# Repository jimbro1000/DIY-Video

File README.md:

# DIY Video #

The DIY Video project is an attempt to define a reusable video "chip" with
modular components. The concept is to limit the design to regular 74LS
ICs.

The goal is a design that can be plugged into most (if not all) 8-bit
computers.

The minimal design permits a system that can switch between a simple
text mode and bitmap mode with a usable screen resolution of 320x200 pixels.
Output is unterminated RGB that can be transformed into an appropriate
format as required

## Design Concepts ##

Each major component of the video system is deliberately isolated so
that a change in one area should not require rework elsewhere. This rule
is broken in some places but is respected as much as possible

The core of the system is a pair of counters that track the X and Y 
position of the "beam". These counters are then used to define the
frame timing (sync and blank) and the viewport position on the screen.

The frame timing also controls what video source makes it to the output
as the sync and blank phases of the signal fall under timing control.

The bitmap renderer uses the pixel counters to generate a palette index
based on either a 1, 2 or 4 bit length value. The index is turned into
RGB using a separate pair of modules that generate 16 distinct RGB values
and a decoder that switches the RGB output between the 16 different
palette options

Independently to all this is the memory controller, actually a repeated
module that provisions different, parallel rendering mechanisms. From
the perspective of the video system each has its own address register
and can be accessed independently of the others - so the bitmap, tile
and sprite data can be operated separately without impacting the timing
of the other.

Externally the different blocks of memory needed to be mapped into the
hosts address space. To facilitate this the different memory blocks
are first selected by a device select signal and are then (optionally)
paged to ease the host burden. 

This approach makes the internal address very wide - each memory block is
a maximum of 32K and with distinct address buses and data buses the burden
for the video system is high but the length and distribution of those
buses can be minimised leaving just the palette values as the the 
interconnect rather than wide data and address buses

The current design respects five different addressable sub-devices
Bitmap memory  
Tile memory  
Sprite memory  
Font generator  
Control registers  

Only the bitmap and control registers are currently implemented.

The font generator in initial design iterations will be a simple eprom that
does not require external addressing

## Roadmap ##

### Stage 1 ###

The initial design stage is to define the hardware and interfaces, the broad
timing requirements and what modules are dependent. The goal is to achieve
a design that can be tested in self-contained modules, that together can
implement a basic bitmap based video generator.

### Stage 2 ###

The initial design will be verified and refined to prove that the modules work.
No attempt to integrate the modules will be attempted at this stage. Signal
and power requirements will be added to the design

### Stage 3 ###

Modules will be implemented as independent PCBs to be re-verified. A backplane
to integrate the modules will be needed with scope to extend the design to 
include other sub-systems

### Stage 4 ###

This is the first opportunity to integrate the entire set of modules defined.
To provide a usable display that can be verified the system will also need
to be integrated with a host computer to drive the video memory content

## Test Progress ##

### Simulation ###

* Position Counters (verilog, CRUMB)
* ViewPort (Verilog)
* Bitmap Data Counters (Verilog)

## License ##

This project is licensed under CC BY-SA 4.0
<https://creativecommons.org/licenses/by-sa/4.0/>

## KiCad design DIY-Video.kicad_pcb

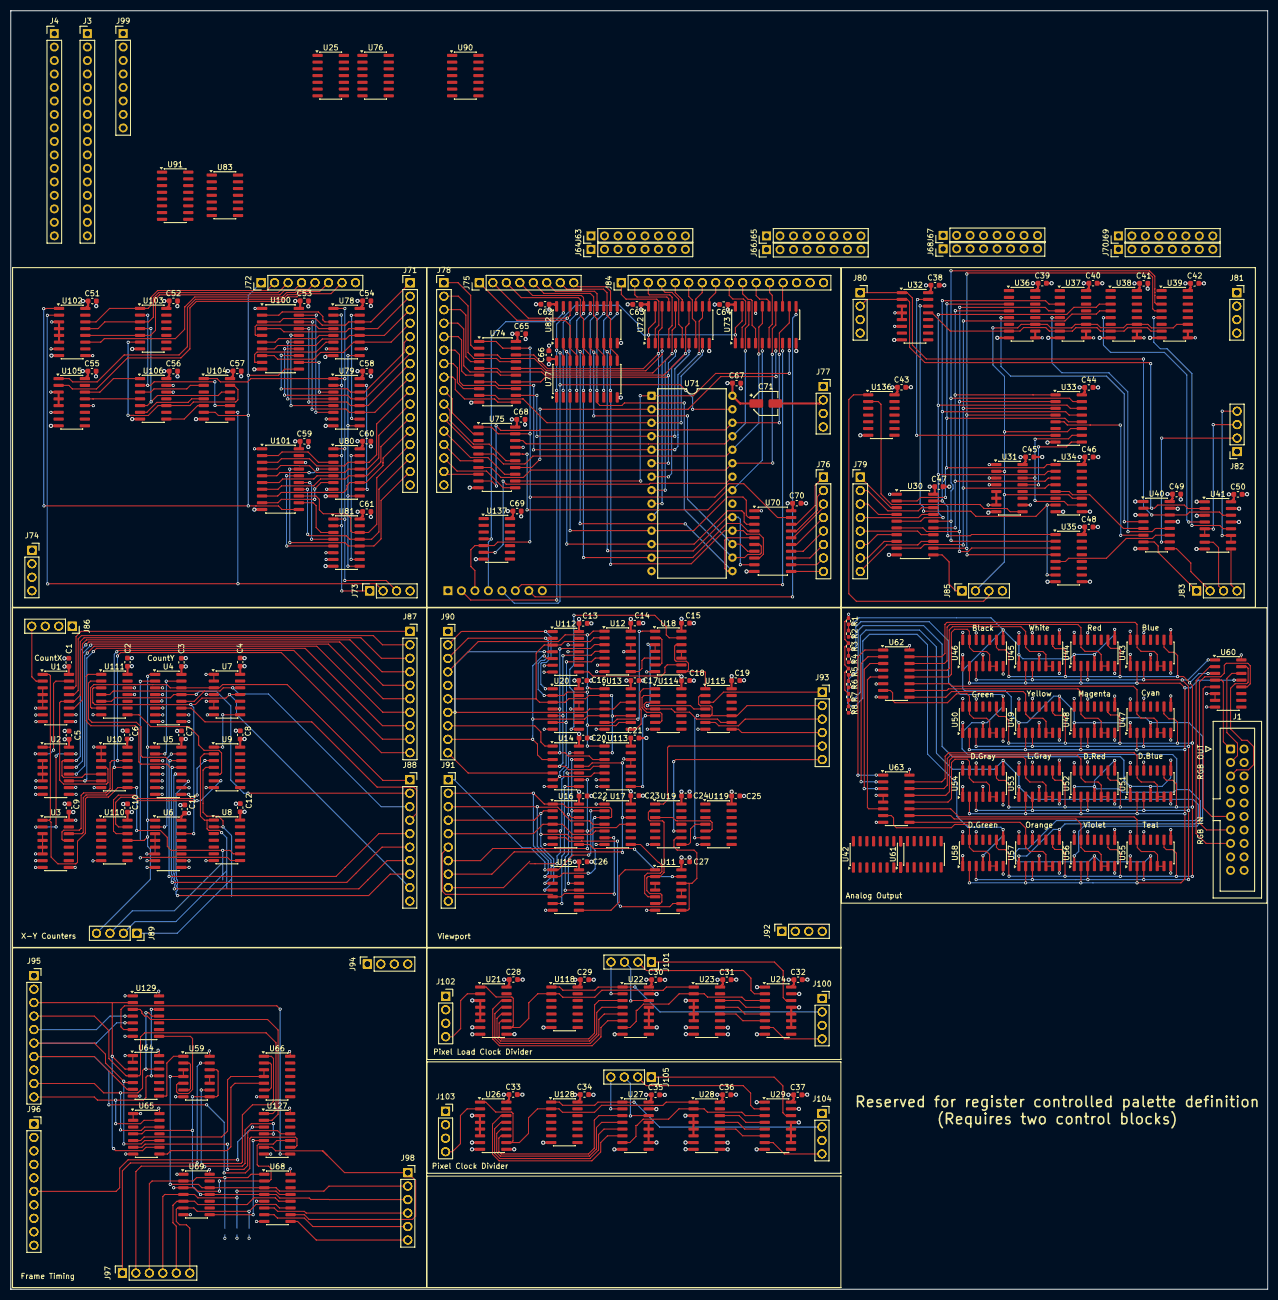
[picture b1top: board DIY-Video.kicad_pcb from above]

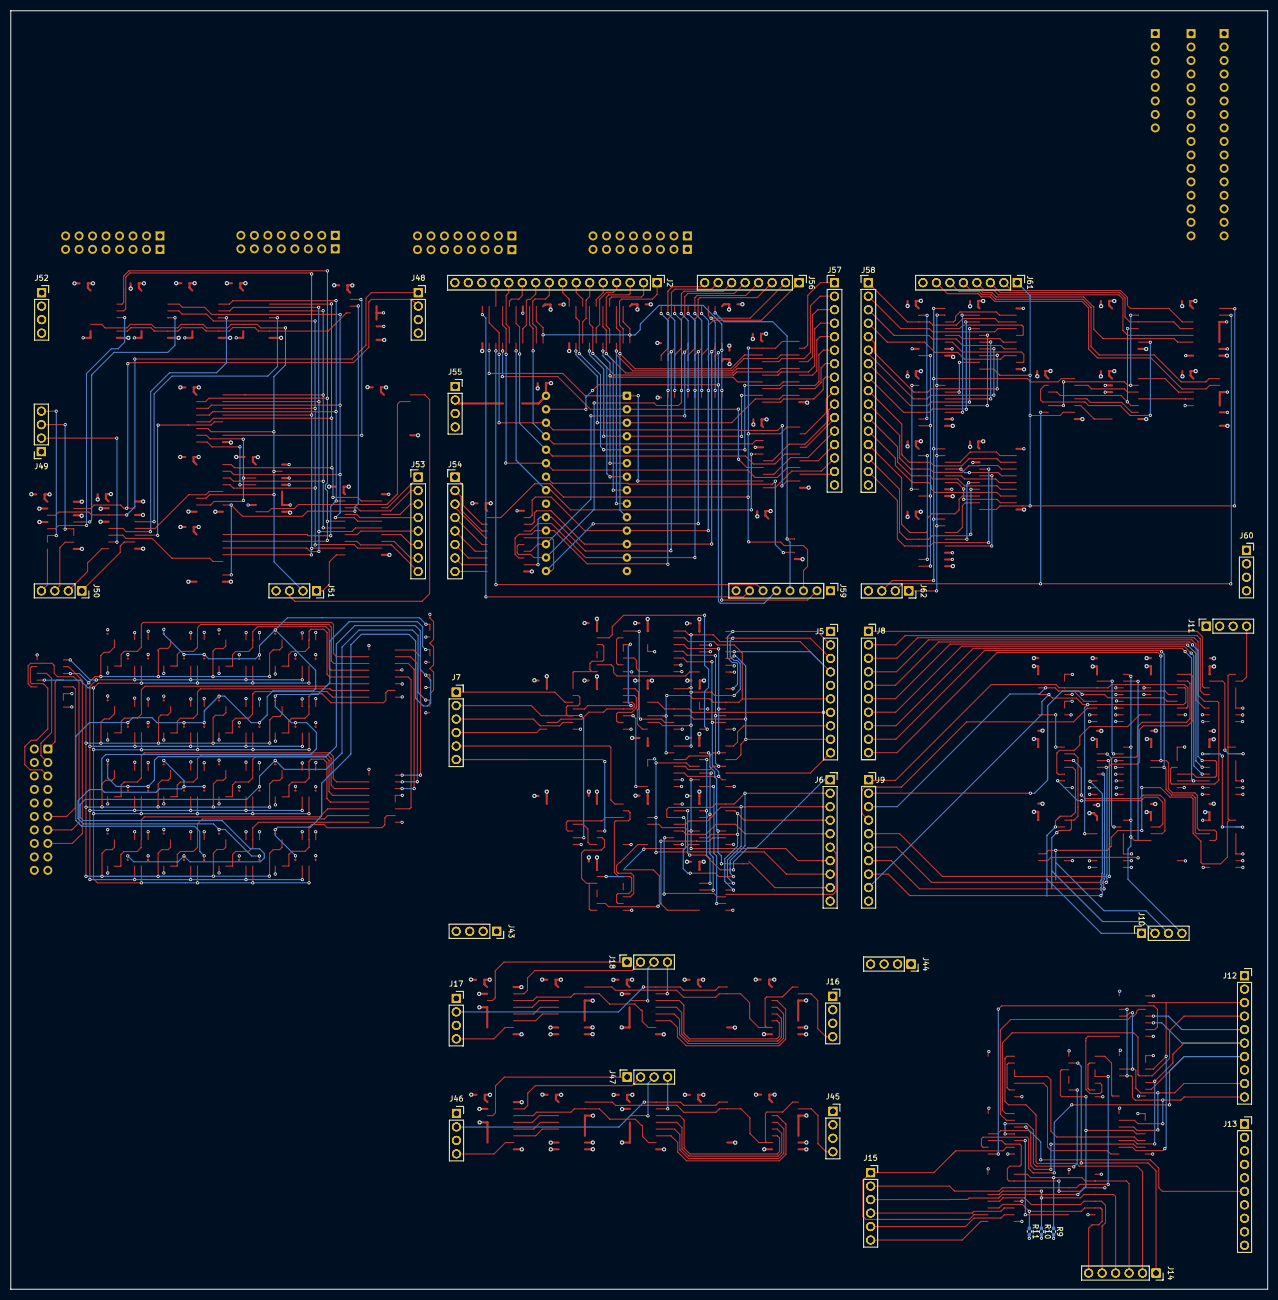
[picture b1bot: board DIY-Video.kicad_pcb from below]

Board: 4 copper layers, 236.8 x 240.9 mm, 315 parts (38 on the bottom side), 422 nets.

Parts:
C1, C2, C3, C4, C5, C6, C7, C8, C9, C10, C11, C12, C13, C14, C15, C16, C17, C18, C19, C20, C21, C22, C23, C24, C25, C26, C27, C28, C29, C30, C31, C32, C33, C34, C35, C36, C37, C38, C39, C40, C41, C42, C43, C44, C45, C46, C47, C48, C49, C50, C51, C52, C53, C54, C55, C56, C57, C58, C59, C60, C61, C62, C63, C64, C65, C66, C67, C68, C69, C70: 10nF; C_0603_1608Metric
C71: 4.7uF; CP_Elec_4x3
J1: VIDEO IO; IDC-Header_2x10_P2.54mm_Vertical
J2, J3, J84: Host Address Bus; PinHeader_1x16_P2.54mm_Vertical
J4: Host Control Bus; PinHeader_1x16_P2.54mm_Vertical
J5, J8, J12, J87, J90, J95: posX; PinSocket_1x10_P2.54mm_Vertical
J6, J9, J13, J88, J91, J96: posY; PinSocket_1x10_P2.54mm_Vertical
J7, J93: ViewportTriggers; PinSocket_1x06_P2.54mm_Vertical
J10, J89: PosResets; PinSocket_1x04_P2.54mm_Vertical
J11, J16, J45, J52, J81, J86, J102, J103: Power and Clock; PinSocket_1x04_P2.54mm_Vertical
J14, J97: TimingTriggers; PinSocket_1x06_P2.54mm_Vertical
J15, J98: ViewportOutput; PinSocket_1x06_P2.54mm_Vertical
J17, J46, J51, J62, J73, J85, J100, J104: Triggers; PinSocket_1x04_P2.54mm_Vertical
J18, J47, J48, J80, J101, J105: OpMode; PinSocket_1x04_P2.54mm_Vertical
J43, J44, J55, J60, J74, J77, J92, J94: Power; PinSocket_1x04_P2.54mm_Vertical
J49, J82: Default Palette; PinSocket_1x04_P2.54mm_Vertical
J50, J83: Output Palette; PinSocket_1x04_P2.54mm_Vertical
J53, J54, J76, J79: BDBus; PinHeader_1x08_P2.54mm_Vertical
J56, J75, J99: XDBus; PinHeader_1x08_P2.54mm_Vertical
J57, J58, J71, J78: BitmapAddress; PinHeader_1x16_P2.54mm_Vertical
J59: Control; PinHeader_1x08_P2.54mm_Vertical
J61, J72: RowCountControl; PinHeader_1x08_P2.54mm_Vertical
J63: Reg0; PinHeader_1x08_P2.54mm_Vertical
J64: Reg1; PinHeader_1x08_P2.54mm_Vertical
J65: Reg2; PinHeader_1x08_P2.54mm_Vertical
J66: Reg3; PinHeader_1x08_P2.54mm_Vertical
J67: Reg4; PinHeader_1x08_P2.54mm_Vertical
J68: Reg5; PinHeader_1x08_P2.54mm_Vertical
J69: Reg6; PinHeader_1x08_P2.54mm_Vertical
J70: Reg7; PinHeader_1x08_P2.54mm_Vertical
NT1, NT2, NT3, NT4, NT5, NT6, NT7, NT8, NT9, NT10, NT11, NT12, NT13, NT14, NT15, NT16, NT17, NT18, NT19, NT20, NT21, NT22, NT23, NT24, NT25, NT26, NT27, NT28, NT29, NT30, NT31, NT32, NT33, NT34, NT35, NT36, NT37, NT38, NT39, NT40, NT41, NT42, NT43, NT44, NT45, NT46, NT47, NT48: NetTie_2; NetTie-2_SMD_Pad0.4mm
R1, R3, R8: 100R; R_0402_1005Metric_Pad0.72x0.64mm_HandSolder
R2, R7: 200R; R_0402_1005Metric_Pad0.72x0.64mm_HandSolder
R4: 75R; R_0402_1005Metric_Pad0.72x0.64mm_HandSolder
R5: 180R; R_0402_1005Metric_Pad0.72x0.64mm_HandSolder
R6: 50R; R_0402_1005Metric_Pad0.72x0.64mm_HandSolder
R9, R10, R11: 4K7; R_0402_1005Metric_Pad0.72x0.64mm_HandSolder
U1, U2, U3, U4, U5, U6, U21, U23, U26, U28, U31, U78, U79, U80, U81, U102: 74LS163; SOIC-16_3.9x9.9mm_P1.27mm
U7, U10, U12, U15, U17, U20, U64, U69, U111, U112, U113, U129: 74LS30; SO-14_3.9x8.65mm_P1.27mm
U8, U14, U76: 74LS04; SO-14_3.9x8.65mm_P1.27mm
U9, U19, U115: 74LS32; SO-14_3.9x8.65mm_P1.27mm
U11, U18, U59, U66, U114: 74LS00; SO-14_3.9x8.65mm_P1.27mm
U13, U16, U65: 74LS20; SO-14_3.9x8.65mm_P1.27mm
U22, U24, U27, U29: 74LS253; SOIC-16_3.9x9.9mm_P1.27mm
U25, U106: 74LS32; SOIC-14_3.9x8.7mm_P1.27mm
U30: 74LS373; SO-20_5.3x12.6mm_P1.27mm
U32, U42, U62, U63, U105: 74LS138; SOIC-16_3.9x9.9mm_P1.27mm
U33, U34, U35, U36, U37, U38, U39: 74LS151; SOIC-16_3.9x9.9mm_P1.27mm
U40, U41: 74LS153; SOIC-16_3.9x9.9mm_P1.27mm
U43, U44, U45, U46, U47, U48, U49, U50, U51, U52, U53, U54, U55, U56, U57, U58: CD4066BM; SO-14_3.9x8.65mm_P1.27mm
U60: 4053; SOIC-16_3.9x9.9mm_P1.27mm
U61: 74LS21; SO-14_3.9x8.65mm_P1.27mm
U68: 74LS148; SOIC-16_3.9x9.9mm_P1.27mm
U70: 74LS245; SO-20_5.3x12.6mm_P1.27mm
U71: CY62256-70PC; DIP-28_W15.24mm
U72, U73, U74, U75, U77, U82: 74LS244; SO-20_5.3x12.6mm_P1.27mm
U83, U90, U110: 74LS08; SO-14_3.9x8.65mm_P1.27mm
U91: 74ALS138; SOIC-16_3.9x9.9mm_P1.27mm
U100, U101: 74LS374; SO-20_5.3x12.6mm_P1.27mm
U103, U118, U127, U128, U136: 74LS04; SOIC-14_3.9x8.7mm_P1.27mm
U104: 74LS21; SOIC-14_3.9x8.7mm_P1.27mm
U119, U137: 74LS08; SOIC-14_3.9x8.7mm_P1.27mm

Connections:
14M: J11.4, J16.4, J45.4, J86.4, J102.4, J103.4, U1.2 (CP), U21.2 (CP), U26.2 (CP)
+1V2: NT25.1, NT26.1, NT27.1, NT47.1, NT48.1, R5.2, R6.1
+1V5: NT31.1, NT36.1, NT38.1, NT41.1, R7.2, R8.1
+2V5: NT23.1, NT24.1, NT28.1, NT29.1, NT30.1, NT43.1, NT45.1, R3.2, R4.1
+3.3V: NT4.1, NT5.1, NT6.1, NT7.1, NT12.1, NT14.1, NT16.1, NT17.1, NT19.1, NT21.1, NT40.1, R1.2, R2.1
+5V: C1.1, C2.1, C3.1, C4.1, C5.1, C6.1, C7.1, C8.1, C9.1, C10.1, C11.1, C12.1, C13.1, C14.1, C15.1, C16.1, C17.1, C18.1, C19.1, C20.1, C21.1, C22.1, C23.1, C24.1, C25.1, C26.1, C27.1, C28.1, C29.1, C30.1, C31.1, C32.1, C33.1, C34.1, C35.1, C36.1, C37.1, C38.1, C39.1, C40.1, C41.1, C42.1, C43.1, C44.1, C45.1, C46.1, C47.1, C48.1, C49.1, C50.1, C51.1, C52.1, C53.1, C54.1, C55.1, C56.1, C57.1, C58.1, C59.1, C60.1, C61.1, C62.1, C63.1, C64.1, C65.1, C66.1, C67.1, C68.1, C69.1, C70.1, C71.1, J4.1, J11.1, J16.1, J43.1, J43.4, J44.1, J44.4, J45.1, J52.1, J55.1, J55.4, J60.1, J60.4, J74.1, J74.4, J77.1, J77.4, J81.1, J86.1, J92.1, J92.4, J94.1, J94.4, J102.1, J103.1, R1.1, R3.1, R5.1, R7.1, U1.7 (CEP), U1.10 (CET), U1.16 (VCC), U2.7 (CEP), U2.10 (CET), U2.16 (VCC), U3.7 (CEP), U3.10 (CET), U3.16 (VCC), U4.7 (CEP), U4.10 (CET), U4.16 (VCC), U5.7 (CEP), U5.10 (CET), U5.16 (VCC), U6.7 (CEP), U6.10 (CET), U6.16 (VCC), U7.1, U7.2, U7.4, U7.5, U7.6, U7.14 (VCC), U8.14 (VCC), U9.14 (VCC), U10.1, U10.2, U10.3, U10.14 (VCC), U11.14 (VCC), U12.6, U12.11, U12.12, U12.14 (VCC), U13.14 (VCC), U14.14 (VCC), U15.14 (VCC), U16.14 (VCC), U17.1, U17.14 (VCC), U18.14 (VCC), U19.14 (VCC), U20.11, U20.12, U20.14 (VCC), U21.7 (CEP), U21.16 (VCC), U22.15 (OEb), U22.16 (VCC), U23.7 (CEP), U23.10 (CET), U23.16 (VCC), U24.15 (OEb), U24.16 (VCC), U25.14 (VCC), U26.7 (CEP), U26.16 (VCC), U27.15 (OEb), U27.16 (VCC), U28.7 (CEP), U28.10 (CET), U28.16 (VCC), U29.15 (OEb), U29.16 (VCC), U30.20 (VCC), U31.1 (~MR), U31.3 (D0), U31.4 (D1), U31.5 (D2), U31.6 (D3), U31.7 (CEP), U31.10 (CET), U31.16 (VCC), U32.6 (E3), U32.16 (VCC), U33.16 (VCC), U34.16 (VCC), U35.16 (VCC), U36.16 (VCC), U37.16 (VCC), U38.16 (VCC), U39.16 (VCC), U40.16 (VCC), U41.16 (VCC), U42.6 (E3), U42.16 (VCC), U43.14 (V_{DD}), U44.14 (V_{DD}), U45.14 (V_{DD}), U46.14 (V_{DD}), U47.14 (V_{DD}), U48.14 (V_{DD}), U49.14 (V_{DD}), U50.14 (V_{DD}), U51.14 (V_{DD}), U52.14 (V_{DD}), U53.14 (V_{DD}), U54.14 (V_{DD}), U55.14 (V_{DD}), U56.14 (V_{DD}), U57.14 (V_{DD}), U58.14 (V_{DD}), U59.14 (VCC), U60.16 (VDD), U61.5, U61.14 (VCC), U62.6 (E3), U62.16 (VCC), U63.16 (VCC), U64.1, U64.2, U64.3, U64.14 (VCC), U65.1, U65.2, U65.14 (VCC), U66.14 (VCC), U68.16 (VCC), U69.1, U69.14 (VCC), U70.1 (A->B), U70.20 (VCC), U71.28 (VCC), U72.20 (VCC), U73.20 (VCC), U74.20 (VCC), U75.20 (VCC), U76.13, U76.14 (VCC), U77.20 (VCC), U78.7 (CEP), U78.10 (CET), U78.16 (VCC), U79.7 (CEP), U79.16 (VCC), U80.7 (CEP), U80.16 (VCC), U81.7 (CEP), U81.16 (VCC), U82.20 (VCC), U83.14 (VCC), U90.14 (VCC), U91.16 (VCC), U100.20 (VCC), U101.20 (VCC), U102.7 (CEP), U102.16 (VCC), U103.13, U103.14 (VCC), U104.14 (VCC), U105.6 (E3), U105.16 (VCC), U106.14 (VCC), U110.14 (VCC), U111.11, U111.12, U111.14 (VCC), U112.6, U112.11, U112.12, U112.14 (VCC), U113.6, U113.11, U113.12, U113.14 (VCC), U114.14 (VCC), U115.14 (VCC), U118.14 (VCC), U119.14 (VCC), U127.14 (VCC), U128.14 (VCC), U129.1, U129.14 (VCC), U136.14 (VCC), U137.14 (VCC)
/A0: J2.1, U72.2 (I0a)
/A1: J2.2, U72.17 (I3b)
/A2: J2.3, U72.4 (I1a)
/A3: J2.4, U72.6 (I2a)
/A4: J2.5, U72.15 (I2b)
/A5: J2.6, U72.8 (I3a)
/A6: J2.7, U72.13 (I1b)
/A7: J2.8, U72.11 (I0b)
/A8: J2.9, U73.2 (I0a)
/A9: J2.10, U73.4 (I1a)
/A10: J2.11, U73.15 (I2b)
/A11: J2.12, U73.6 (I2a)
/A12: J2.13, U73.13 (I1b)
/A13: J2.14, U90.2
/A14: J2.15, U90.10
/BitmapAddressRegister/CA0: U78.15 (TC), U79.10 (CET)
/BitmapAddressRegister/CA1: U79.15 (TC), U80.10 (CET)
/BitmapAddressRegister/CA2: U80.15 (TC), U81.10 (CET)
/BitmapAddressRegister/IBA0: J57.1, J58.1, U74.2 (I0a), U78.14 (Q0), U100.3 (D0)
/BitmapAddressRegister/IBA1: J57.2, J58.2, U74.17 (I3b), U78.13 (Q1), U100.4 (D1)
/BitmapAddressRegister/IBA2: J57.3, J58.3, U74.4 (I1a), U78.12 (Q2), U100.7 (D2)
/BitmapAddressRegister/IBA3: J57.4, J58.4, U74.15 (I2b), U78.11 (Q3), U100.8 (D3)
/BitmapAddressRegister/IBA4: J57.5, J58.5, U74.6 (I2a), U79.14 (Q0), U100.13 (D4)
/BitmapAddressRegister/IBA5: J57.6, J58.6, U74.13 (I1b), U79.13 (Q1), U100.14 (D5)
/BitmapAddressRegister/IBA6: J57.7, J58.7, U74.8 (I3a), U79.12 (Q2), U100.17 (D6)
/BitmapAddressRegister/IBA7: J57.8, J58.8, U74.11 (I0b), U79.11 (Q3), U100.18 (D7)
/BitmapAddressRegister/IBA8: J57.9, J58.9, U75.2 (I0a), U80.14 (Q0), U101.3 (D0)
/BitmapAddressRegister/IBA9: J57.10, J58.10, U75.15 (I2b), U80.13 (Q1), U101.4 (D1)
/BitmapAddressRegister/IBA10: J57.11, J58.11, U75.4 (I1a), U80.12 (Q2), U101.7 (D2)
/BitmapAddressRegister/IBA11: J57.12, J58.12, U75.13 (I1b), U80.11 (Q3), U101.8 (D3)
/BitmapAddressRegister/IBA12: J57.13, J58.13, U75.6 (I2a), U81.14 (Q0), U101.13 (D4)
/BitmapAddressRegister/IBA13: J57.14, J58.14, U75.11 (I0b), U81.13 (Q1), U101.14 (D5)
/BitmapAddressRegister/IBA14: J57.15, J58.15, U75.8 (I3a), U81.12 (Q2), U101.17 (D6)
/BitmapAddressRegister/RA0: U78.3 (D0), U100.2 (O0)
/BitmapAddressRegister/RA1: U78.4 (D1), U100.5 (O1)
/BitmapAddressRegister/RA2: U78.5 (D2), U100.6 (O2)
/BitmapAddressRegister/RA3: U78.6 (D3), U100.9 (O3)
/BitmapAddressRegister/RA4: U79.3 (D0), U100.12 (O4)
/BitmapAddressRegister/RA5: U79.4 (D1), U100.15 (O5)
/BitmapAddressRegister/RA6: U79.5 (D2), U100.16 (O6)
/BitmapAddressRegister/RA7: U79.6 (D3), U100.19 (O7)
/BitmapAddressRegister/RA8: U80.3 (D0), U101.2 (O0)
/BitmapAddressRegister/RA9: U80.4 (D1), U101.5 (O1)
/BitmapAddressRegister/RA10: U80.5 (D2), U101.6 (O2)
/BitmapAddressRegister/RA11: U80.6 (D3), U101.9 (O3)
/BitmapAddressRegister/RA12: U81.3 (D0), U101.12 (O4)
/BitmapAddressRegister/RA13: U81.4 (D1), U101.15 (O5)
/BitmapAddressRegister/RA14: U81.5 (D2), U101.16 (O6)
/BitmapAddressRegister/RC0: J61.2, U102.14 (Q0), U103.1
/BitmapAddressRegister/RC1: J61.3, U102.13 (Q1), U103.3
/BitmapAddressRegister/RC2: J61.4, U102.12 (Q2), U103.5
/BitmapAddressRegister/RC3: J61.5, U102.11 (Q3)
/BitmapAddressRegister/RR0: J61.6, U105.1 (A0)
/BitmapAddressRegister/RR1: J61.7, U105.2 (A1)
/BitmapAddressRegister/Reload: U78.9 (~PE), U79.9 (~PE), U80.9 (~PE), U81.9 (~PE), U104.8
/BitmapAddressRegister/~RC0: U103.2, U104.10, U106.2
/BitmapAddressRegister/~RC1: U103.4, U104.12, U106.5
/BitmapAddressRegister/~RC2: U103.6, U104.13, U106.10
/BitmapAddressRegister/~RRMR: J61.1, U100.11 (Cp), U101.11 (Cp), U102.1 (~MR), U104.6
/BitmapAddressRegister/~Reset2: U104.2, U106.3
/BitmapAddressRegister/~Reset4: U104.4, U106.6
/BitmapAddressRegister/~Reset8: U104.5, U106.8
/BitmapDataCounter/2T: U21.14 (Q0), U22.6 (I0a)
/BitmapDataCounter/4T: U21.13 (Q1), U22.5 (I1a)
/BitmapDataCounter/8T: U21.12 (Q2), U22.4 (I2a)
/BitmapDataCounter/16T: U21.11 (Q3), U22.3 (I3a)
/BitmapDataCounter/BPP0: J18.1, J47.1, J48.1, U24.14 (A0), U29.14 (A0), U32.1 (A0), U40.14 (S0), U41.14 (S0)
/BitmapDataCounter/BPP1: J18.2, J47.2, J48.2, U24.2 (A1), U29.2 (A1), U32.2 (A1), U40.2 (S1), U41.2 (S1)
/BitmapDataCounter/CPP0: J18.3, J47.3, U22.14 (A0), U27.14 (A0)
/BitmapDataCounter/CPP1: J18.4, J47.4, U22.2 (A1), U27.2 (A1)
/BitmapDataCounter/LoadEnable: U21.1 (~MR), U21.10 (CET), U23.1 (~MR), U118.2
/BitmapDataCounter/PT0: U22.7 (Za), U23.2 (CP), U24.3 (I3a)
/BitmapDataCounter/PT1: U23.14 (Q0), U24.4 (I2a)
/BitmapDataCounter/PT2: U23.13 (Q1), U24.5 (I1a)
/BitmapDataCounter/PT3: U23.12 (Q2), U24.6 (I0a)
/BitmapMemory/BA0: U71.10 (A0), U72.18 (O0a), U74.18 (O0a)
/BitmapMemory/BA1: U71.9 (A1), U72.3 (O3b), U74.3 (O3b)
/BitmapMemory/BA2: U71.8 (A2), U72.16 (O1a), U74.16 (O1a)
/BitmapMemory/BA3: U71.7 (A3), U72.14 (O2a), U74.5 (O2b)
/BitmapMemory/BA4: U71.6 (A4), U72.5 (O2b), U74.14 (O2a)
/BitmapMemory/BA5: U71.5 (A5), U72.12 (O3a), U74.7 (O1b)
/BitmapMemory/BA6: U71.4 (A6), U72.7 (O1b), U74.12 (O3a)
/BitmapMemory/BA7: U71.3 (A7), U72.9 (O0b), U74.9 (O0b)
/BitmapMemory/BA8: U71.25 (A8), U73.18 (O0a), U75.18 (O0a)
/BitmapMemory/BA9: U71.24 (A9), U73.16 (O1a), U75.5 (O2b)
/BitmapMemory/BA10: U71.21 (A10), U73.5 (O2b), U75.16 (O1a)
/BitmapMemory/BA11: U71.23 (A11), U73.14 (O2a), U75.7 (O1b)
/BitmapMemory/BA12: U71.2 (A12), U73.7 (O1b), U75.14 (O2a)
/BitmapMemory/BA13: U71.26 (A13), U73.12 (O3a), U75.9 (O0b)
/BitmapMemory/BA14: U71.1 (A14), U73.9 (O0b), U75.12 (O3a)
/BitmapMemory/BD0: J53.1, J54.1, U30.3 (D0), U70.18 (B0)
/BitmapMemory/BD1: J53.2, J54.2, U30.18 (D7), U70.17 (B1)
/BitmapMemory/BD2: J53.3, J54.3, U30.4 (D1), U70.16 (B2)
/BitmapMemory/BD3: J53.4, J54.4, U30.17 (D6), U70.15 (B3)
/BitmapMemory/BD4: J53.5, J54.5, U30.14 (D5), U70.14 (B4)
/BitmapMemory/BD5: J53.6, J54.6, U30.7 (D2), U70.13 (B5)
/BitmapMemory/BD6: J53.7, J54.7, U30.8 (D3), U70.12 (B6)
/BitmapMemory/BD7: J53.8, J54.8, U30.13 (D4), U70.11 (B7)
/BitmapMemory/D0: U70.2 (A0), U71.11 (Q0), U77.3 (O3b), U82.17 (I3b)
/BitmapMemory/D1: U70.3 (A1), U71.12 (Q1), U77.18 (O0a), U82.2 (I0a)
/BitmapMemory/D2: U70.4 (A2), U71.13 (Q2), U77.5 (O2b), U82.15 (I2b)
/BitmapMemory/D3: U70.5 (A3), U71.15 (Q3), U77.16 (O1a), U82.4 (I1a)
/BitmapMemory/D4: U70.6 (A4), U71.16 (Q4), U77.7 (O1b), U82.13 (I1b)
/BitmapMemory/D5: U70.7 (A5), U71.17 (Q5), U77.14 (O2a), U82.6 (I2a)
/BitmapMemory/D6: U70.8 (A6), U71.18 (Q6), U77.9 (O0b), U82.11 (I0b)
/BitmapMemory/D7: U70.9 (A7), U71.19 (Q7), U77.12 (O3a), U82.8 (I3a)
/BitmapPixelCounter/2T: U26.14 (Q0), U27.6 (I0a)
/BitmapPixelCounter/4T: U26.13 (Q1), U27.5 (I1a)
/BitmapPixelCounter/8T: U26.12 (Q2), U27.4 (I2a)
/BitmapPixelCounter/16T: U26.11 (Q3), U27.3 (I3a)
/BitmapPixelCounter/CountEnable: U26.1 (~MR), U26.10 (CET), U28.1 (~MR), U128.2
/BitmapPixelCounter/PT0: U27.7 (Za), U28.2 (CP), U29.3 (I3a)
/BitmapPixelCounter/PT1: U28.14 (Q0), U29.4 (I2a)
/BitmapPixelCounter/PT2: U28.13 (Q1), U29.5 (I1a)
/BitmapPixelCounter/PT3: U28.12 (Q2), U29.6 (I0a)
/BitmapPixelData/BMPalette0: J50.1, U40.7 (Za)
/BitmapPixelData/BMPalette1: J50.2, U40.9 (Zb)
/BitmapPixelData/BMPalette2: J50.3, U41.7 (Za)
/BitmapPixelData/BMPalette3: J50.4, U41.9 (Zb)
/BitmapPixelData/BPP1Palette0: U33.5 (Z), U40.6 (I0a)
/BitmapPixelData/BPP2Palette0: U34.5 (Z), U40.5 (I1a)
/BitmapPixelData/BPP2Palette1: U35.5 (Z), U40.11 (I1b)
/BitmapPixelData/BPP4Palette0: U36.5 (Z), U40.4 (I2a)
/BitmapPixelData/BPP4Palette1: U37.5 (Z), U40.12 (I2b)
/BitmapPixelData/BPP4Palette2: U38.5 (Z), U41.4 (I2a)
/BitmapPixelData/BPP4Palette3: U39.5 (Z), U41.12 (I2b)
/BitmapPixelData/D0: U30.2 (O0), U33.12 (I7), U34.1 (I3), U36.3 (I1)
/BitmapPixelData/D1: U30.19 (O7), U33.13 (I6), U35.1 (I3), U37.3 (I1)
/BitmapPixelData/D2: U30.5 (O1), U33.14 (I5), U34.2 (I2), U38.3 (I1)
/BitmapPixelData/D3: U30.16 (O6), U33.15 (I4), U35.2 (I2), U39.3 (I1)
/BitmapPixelData/D4: U30.15 (O5), U33.1 (I3), U34.3 (I1), U36.4 (I0)
/BitmapPixelData/D5: U30.6 (O2), U33.2 (I2), U35.3 (I1), U37.4 (I0)
/BitmapPixelData/D6: U30.9 (O3), U33.3 (I1), U34.4 (I0), U38.4 (I0)
/BitmapPixelData/D7: U30.12 (O4), U33.4 (I0), U35.4 (I0), U39.4 (I0)
/BitmapPixelData/DefaultPalette1: J49.2, U40.10 (I0b)
/BitmapPixelData/DefaultPalette2: J49.3, U41.5 (I1a), U41.6 (I0a)
/BitmapPixelData/DefaultPalette3: J49.4, U41.10 (I0b), U41.11 (I1b)
/BitmapPixelData/PT1: U31.14 (Q0), U33.10 (S1), U34.10 (S1), U35.10 (S1)
/BitmapPixelData/PT2: U31.13 (Q1), U33.9 (S2)
/BitmapPixelData/Pattern0: U32.15 (O0), U33.7 (~E)
/BitmapPixelData/Pattern1: U32.14 (O1), U34.7 (~E), U35.7 (~E)
/BitmapPixelData/Pattern2: U32.13 (O2), U36.7 (~E), U37.7 (~E), U38.7 (~E), U39.7 (~E)
/BitmapPixelData/~MR: U31.9 (~PE), U136.2
/ControlRegisters/PageSize0: U76.5, U90.4
/ControlRegisters/PageSize1: U76.9, U90.12
/ControlRegisters/~PageSize0: U76.6, U90.1
/ControlRegisters/~PageSize1: U76.8, U90.9
/ControlRegisters/~SelectRegister5: U25.9, U25.12
/FrameTiming/VSource0: J15.6, U42.1 (A0), U68.9 (S0)
/FrameTiming/VSource1: J15.5, U42.2 (A1), U68.7 (S1)
/FrameTiming/VSource2: J15.4, U42.3 (A2), U68.6 (S2)
/FrameTiming/X0: J5.1, J8.1, J12.1, U1.14 (Q0)
/FrameTiming/X1: J5.2, J8.2, J12.2, U1.13 (Q1), U20.1, U112.1
/FrameTiming/X2: J5.3, J8.3, J12.3, U1.12 (Q2), U10.4, U13.9, U20.2, U65.9, U112.2, U113.1, U129.2
/FrameTiming/X3: J5.4, J8.4, J12.4, U1.11 (Q3), U12.1, U13.1, U64.4, U127.1
/FrameTiming/X4: J5.5, J8.5, J12.5, U2.14 (Q0), U10.5, U129.4
/FrameTiming/X5: J5.6, J8.6, J12.6, U2.13 (Q1), U12.2, U13.2, U13.10, U20.3, U64.5, U65.10, U112.3, U113.2, U129.5
/FrameTiming/X6: J5.7, J8.7, J12.7, U2.12 (Q2), U13.4, U13.12, U64.6, U112.4, U127.9
/FrameTiming/X7: J5.8, J8.8, J12.8, U2.11 (Q3), U10.6, U14.1
/FrameTiming/X8: J5.9, J8.9, J12.9, U3.14 (Q0), U10.11, U13.5, U13.13, U14.3, U64.12, U65.12, U112.5, U129.11
/FrameTiming/X9: J5.10, J8.10, J12.10, U3.13 (Q1), U10.12, U14.5, U64.11, U65.13, U129.12
/FrameTiming/Y0: J6.1, J9.1, J13.1, U4.14 (Q0), U7.3, U15.1, U17.2, U111.6
/FrameTiming/Y1: J6.2, J9.2, J13.2, U4.13 (Q1), U15.2, U16.1, U17.3, U111.5
/FrameTiming/Y2: J6.3, J9.3, J13.3, U4.12 (Q2), U7.12, U15.3, U17.4, U111.4
/FrameTiming/Y3: J6.4, J9.4, J13.4, U4.11 (Q3), U15.4, U16.2, U16.9
/FrameTiming/Y4: J6.5, J9.5, J13.5, U5.14 (Q0), U16.4, U17.5, U111.2
/FrameTiming/Y5: J6.6, J9.6, J13.6, U5.13 (Q1), U15.5, U17.6, U111.1, U127.3
/FrameTiming/Y6: J6.7, J9.7, J13.7, U5.12 (Q2), U14.9, U16.10, U17.11
/FrameTiming/Y7: J6.8, J9.8, J13.8, U5.11 (Q3), U14.11, U17.12
/FrameTiming/Y8: J6.9, J9.9, J13.9, U6.14 (Q0), U7.11, U14.13, U16.5, U111.3
/PaletteGenerator/PB0: NT3.2, U43.8
/PaletteGenerator/PB1: NT6.2, U44.8
/PaletteGenerator/PB2: NT9.2, U45.8
/PaletteGenerator/PB3: NT12.2, U46.8
/PaletteGenerator/PB4: NT15.2, U47.8
/PaletteGenerator/PB5: NT18.2, U48.8
/PaletteGenerator/PB6: NT21.2, U49.8
/PaletteGenerator/PB7: NT24.2, U50.8
/PaletteGenerator/PB8: NT27.2, U51.8
/PaletteGenerator/PB9: NT30.2, U52.8
/PaletteGenerator/PB10: NT33.2, U53.8
/PaletteGenerator/PB11: NT36.2, U54.8
/PaletteGenerator/PB12: NT39.2, U55.8
/PaletteGenerator/PB13: NT42.2, U56.8
/PaletteGenerator/PB14: NT45.2, U57.8
/PaletteGenerator/PB15: NT48.2, U58.8
/PaletteGenerator/PG0: NT2.2, U43.4
/PaletteGenerator/PG1: NT5.2, U44.4
/PaletteGenerator/PG2: NT8.2, U45.4
/PaletteGenerator/PG3: NT11.2, U46.4
/PaletteGenerator/PG4: NT14.2, U47.4
/PaletteGenerator/PG5: NT17.2, U48.4
/PaletteGenerator/PG6: NT20.2, U49.4
/PaletteGenerator/PG7: NT23.2, U50.4
/PaletteGenerator/PG8: NT26.2, U51.4
/PaletteGenerator/PG9: NT29.2, U52.4
/PaletteGenerator/PG10: NT32.2, U53.4
/PaletteGenerator/PG11: NT35.2, U54.4
/PaletteGenerator/PG12: NT38.2, U55.4
/PaletteGenerator/PG13: NT41.2, U56.4
/PaletteGenerator/PG14: NT44.2, U57.4
/PaletteGenerator/PG15: NT47.2, U58.4
/PaletteGenerator/PR0: NT1.2, U43.1
/PaletteGenerator/PR1: NT4.2, U44.1
/PaletteGenerator/PR2: NT7.2, U45.1
/PaletteGenerator/PR3: NT10.2, U46.1
/PaletteGenerator/PR4: NT13.2, U47.1
/PaletteGenerator/PR5: NT16.2, U48.1
/PaletteGenerator/PR6: NT19.2, U49.1
/PaletteGenerator/PR7: NT22.2, U50.1
/PaletteGenerator/PR8: NT25.2, U51.1
/PaletteGenerator/PR9: NT28.2, U52.1
/PaletteGenerator/PR10: NT31.2, U53.1
/PaletteGenerator/PR11: NT34.2, U54.1
/PaletteGenerator/PR12: NT37.2, U55.1
/PaletteGenerator/PR13: NT40.2, U56.1
/PaletteGenerator/PR14: NT43.2, U57.1
/PaletteGenerator/PR15: NT46.2, U58.1
/PaletteMultiplexer/ISource0: U43.2, U44.2, U45.2, U46.2, U47.2, U48.2, U49.2, U50.2, U51.2, U52.2, U53.2, U54.2, U55.2, U56.2, U57.2, U58.2, U60.13 (X1)
/PaletteMultiplexer/ISource1: U43.3, U44.3, U45.3, U46.3, U47.3, U48.3, U49.3, U50.3, U51.3, U52.3, U53.3, U54.3, U55.3, U56.3, U57.3, U58.3, U60.1 (Y1)
/PaletteMultiplexer/ISource2: U43.9, U44.9, U45.9, U46.9, U47.9, U48.9, U49.9, U50.9, U51.9, U52.9, U53.9, U54.9, U55.9, U56.9, U57.9, U58.9, U60.3 (Z1)
/PaletteMultiplexer/PaletteEn0: U43.5, U43.6, U43.13, U62.15 (O0)
/PaletteMultiplexer/PaletteEn1: U44.5, U44.6, U44.13, U62.14 (O1)
/PaletteMultiplexer/PaletteEn2: U45.5, U45.6, U45.13, U62.13 (O2)
/PaletteMultiplexer/PaletteEn3: U46.5, U46.6, U46.13, U62.12 (O3)
/PaletteMultiplexer/PaletteEn4: U47.5, U47.6, U47.13, U62.11 (O4)
/PaletteMultiplexer/PaletteEn5: U48.5, U48.6, U48.13, U62.10 (O5)
/PaletteMultiplexer/PaletteEn6: U49.5, U49.6, U49.13, U62.9 (O6)
/PaletteMultiplexer/PaletteEn7: U50.5, U50.6, U50.13, U62.7 (O7)
/PaletteMultiplexer/PaletteEn8: U51.5, U51.6, U51.13, U63.15 (O0)
/PaletteMultiplexer/PaletteEn9: U52.5, U52.6, U52.13, U63.14 (O1)
/PaletteMultiplexer/PaletteEn10: U53.5, U53.6, U53.13, U63.13 (O2)
/PaletteMultiplexer/PaletteEn11: U54.5, U54.6, U54.13, U63.12 (O3)
/PaletteMultiplexer/PaletteEn12: U55.5, U55.6, U55.13, U63.11 (O4)
/PaletteMultiplexer/PaletteEn13: U56.5, U56.6, U56.13, U63.10 (O5)
/PaletteMultiplexer/PaletteEn14: U57.5, U57.6, U57.13, U63.9 (O6)
/PaletteMultiplexer/PaletteEn15: U58.5, U58.6, U58.13, U63.7 (O7)
/PaletteMultiplexer/SelPalette0: U62.1 (A0), U63.1 (A0)
/PaletteMultiplexer/SelPalette1: U62.2 (A1), U63.2 (A1)
/PaletteMultiplexer/SelPalette2: U62.3 (A2), U63.3 (A2)
/PaletteMultiplexer/SelPalette3: U62.5 (E2), U63.6 (E3)
/PaletteMultiplexer/V0: U42.15 (O0), U60.9 (C), U60.10 (B), U60.11 (A), U61.1
/PaletteMultiplexer/V1: U42.14 (O1), U61.2
/PaletteMultiplexer/V2: U42.13 (O2), U61.4
/PositionCounters/CX0: U1.15 (TC), U2.2 (CP)
/PositionCounters/CX1: U2.15 (TC), U3.2 (CP)
/PositionCounters/CY0: U4.15 (TC), U5.2 (CP)
/PositionCounters/CY1: U5.15 (TC), U6.2 (CP)
/PositionCounters/NTSC_RY: U7.8, U9.1
/PositionCounters/PAL_RY: U9.5, U111.8
/PositionCounters/ResetX: U4.2 (CP), U8.8
/RGB0: J1.3, U60.14 (X)
/RGB1: J1.5, U60.15 (Y)
/RGB2: J1.1, U60.4 (Z)
/RegisterInterface/A0: J3.1, J84.1
/RegisterInterface/A1: J3.2, J84.2
/RegisterInterface/A2: J3.3, J84.3
/RegisterInterface/A3: J3.4, J84.4
/RegisterInterface/A4: J3.5, J84.5
/RegisterInterface/A5: J3.6, J84.6
/RegisterInterface/A6: J3.7, J84.7
/RegisterInterface/A7: J3.8, J84.8
/RegisterInterface/A8: J3.9, J84.9
/RegisterInterface/A9: J3.10, J84.10
/RegisterInterface/A10: J3.11, J84.11
/RegisterInterface/A11: J3.12, J84.12
/RegisterInterface/A12: J3.13, J84.13
/RegisterInterface/A13: J3.14, J84.14
/RegisterInterface/A14: J3.15, J84.15
/RegisterInterface/A15: J3.16, J84.16
/RegisterInterface/BD0: J76.1, J79.1
/RegisterInterface/BD1: J76.2, J79.2
/RegisterInterface/BD2: J76.3, J79.3
/RegisterInterface/BD3: J76.4, J79.4
/RegisterInterface/BD4: J76.5, J79.5
/RegisterInterface/BD5: J76.6, J79.6
/RegisterInterface/BD6: J76.7, J79.7
/RegisterInterface/BD7: J76.8, J79.8
/RegisterInterface/BPP0: J63.5, J80.1, J101.1, J105.1
/RegisterInterface/BPP1: J63.6, J80.2, J101.2, J105.2
/RegisterInterface/CPP0: J63.7, J101.3, J105.3
/RegisterInterface/CPP1: J63.8, J101.4, J105.4
/RegisterInterface/IBA0: J71.1, J78.1
/RegisterInterface/IBA1: J71.2, J78.2
/RegisterInterface/IBA2: J71.3, J78.3
/RegisterInterface/IBA3: J71.4, J78.4
/RegisterInterface/IBA4: J71.5, J78.5
/RegisterInterface/IBA5: J71.6, J78.6
/RegisterInterface/IBA6: J71.7, J78.7
/RegisterInterface/IBA7: J71.8, J78.8
/RegisterInterface/IBA8: J71.9, J78.9
/RegisterInterface/IBA9: J71.10, J78.10
/RegisterInterface/IBA10: J71.11, J78.11
/RegisterInterface/IBA11: J71.12, J78.12
/RegisterInterface/IBA12: J71.13, J78.13
/RegisterInterface/IBA13: J71.14, J78.14
/RegisterInterface/IBA14: J71.15, J78.15
/RegisterInterface/RR0: J64.2, J72.6
/RegisterInterface/RR1: J64.3, J72.7
/RegisterInterface/X0: J87.1, J90.1, J95.1
/RegisterInterface/X1: J87.2, J90.2, J95.2
/RegisterInterface/X2: J87.3, J90.3, J95.3
/RegisterInterface/X3: J87.4, J90.4, J95.4
/RegisterInterface/X4: J87.5, J90.5, J95.5
/RegisterInterface/X5: J87.6, J90.6, J95.6
/RegisterInterface/X6: J87.7, J90.7, J95.7
/RegisterInterface/X7: J87.8, J90.8, J95.8
/RegisterInterface/X8: J87.9, J90.9, J95.9
/RegisterInterface/X9: J87.10, J90.10, J95.10
/RegisterInterface/XD0: J75.1, J99.1
/RegisterInterface/XD1: J75.2, J99.2
/RegisterInterface/XD2: J75.3, J99.3
/RegisterInterface/XD3: J75.4, J99.4
/RegisterInterface/XD4: J75.5, J99.5
/RegisterInterface/XD5: J75.6, J99.6
/RegisterInterface/XD6: J75.7, J99.7
/RegisterInterface/XD7: J75.8, J99.8
/RegisterInterface/Y0: J88.1, J91.1, J96.1
/RegisterInterface/Y1: J88.2, J91.2, J96.2
/RegisterInterface/Y2: J88.3, J91.3, J96.3
/RegisterInterface/Y3: J88.4, J91.4, J96.4
/RegisterInterface/Y4: J88.5, J91.5, J96.5
/RegisterInterface/Y5: J88.6, J91.6, J96.6
/RegisterInterface/Y6: J88.7, J91.7, J96.7
/RegisterInterface/Y7: J88.8, J91.8, J96.8
/RegisterInterface/Y8: J88.9, J91.9, J96.9
/ViewPort/HEnd: U13.6, U18.1
/ViewPort/HStart: U12.8, U18.5
/ViewPort/NTSCVEnd: U11.5, U17.8
/ViewPort/NTSCVStart: U11.1, U15.8
/ViewPort/PALVEnd: U11.9, U16.6
/ViewPort/PALVStart: U11.13, U16.8
/ViewPort/~NTSCVCountEnable: U11.2, U11.6, U19.2
/ViewPort/~PALVCountEnable: U11.8, U11.12, U19.9
/ViewPort/~X7: U12.3, U14.2, U20.4, U113.3
/ViewPort/~X8: U12.4, U14.4, U20.5, U113.4
/ViewPort/~X9: U12.5, U14.6, U20.6, U113.5
/ViewPort/~Y6: U14.8, U15.6
/ViewPort/~Y7: U14.10, U15.11, U16.12
/ViewPort/~Y8: U14.12, U15.12, U16.13
/XD0: J56.1, U77.17 (I3b), U82.3 (O3b)
/XD1: J56.2, U77.2 (I0a), U82.18 (O0a)
/XD2: J56.3, U77.15 (I2b), U82.5 (O2b)
/XD3: J56.4, U77.4 (I1a), U82.16 (O1a)
/XD4: J56.5, U77.13 (I1b), U82.7 (O1b)
/XD5: J56.6, U77.6 (I2a), U82.14 (O2a)
/XD6: J56.7, U77.11 (I0b), U82.9 (O0b)
/XD7: J56.8, U77.8 (I3a), U82.12 (O3a)
/XRGB0: J1.13, U60.12 (X0)
/XRGB1: J1.15, U60.2 (Y0)
/XRGB2: J1.11, U60.5 (Z0)
DevSel0: J4.5, U83.10
DevSel4: J4.9, U91.6 (E3)
Format: J7.5, J10.2, J65.5, J89.2, J93.5, U8.1, U9.2, U19.1
GND: C1.2, C2.2, C3.2, C4.2, C5.2, C6.2, C7.2, C8.2, C9.2, C10.2, C11.2, C12.2, C13.2, C14.2, C15.2, C16.2, C17.2, C18.2, C19.2, C20.2, C21.2, C22.2, C23.2, C24.2, C25.2, C26.2, C27.2, C28.2, C29.2, C30.2, C31.2, C32.2, C33.2, C34.2, C35.2, C36.2, C37.2, C38.2, C39.2, C40.2, C41.2, C42.2, C43.2, C44.2, C45.2, C46.2, C47.2, C48.2, C49.2, C50.2, C51.2, C52.2, C53.2, C54.2, C55.2, C56.2, C57.2, C58.2, C59.2, C60.2, C61.2, C62.2, C63.2, C64.2, C65.2, C66.2, C67.2, C68.2, C69.2, C70.2, C71.2, J1.2, J1.4, J1.6, J1.8, J1.10, J1.12, J1.14, J1.16, J1.18, J1.20, J4.16, J11.2, J11.3, J16.2, J16.3, J17.1, J17.3, J43.2, J43.3, J44.2, J44.3, J45.2, J45.3, J46.1, J46.3, J52.2, J52.3, J55.2, J55.3, J60.2, J60.3, J74.2, J74.3, J77.2, J77.3, J81.2, J81.3, J86.2, J86.3, J92.2, J92.3, J94.2, J94.3, J100.1, J100.3, J102.2, J102.3, J103.2, J103.3, J104.1, J104.3, NT1.1, NT2.1, NT3.1, NT8.1, NT9.1, NT10.1, NT11.1, NT13.1, NT15.1, NT18.1, NT20.1, NT22.1, NT32.1, NT33.1, NT34.1, NT35.1, NT37.1, NT39.1, NT42.1, NT44.1, NT46.1, R2.2, R4.2, R6.2, R8.2, R9.2, R10.2, R11.2, U1.3 (D0), U1.4 (D1), U1.5 (D2), U1.6 (D3), U1.8 (GND), U1.9 (~PE), U2.3 (D0), U2.4 (D1), U2.5 (D2), U2.6 (D3), U2.8 (GND), U2.9 (~PE), U3.3 (D0), U3.4 (D1), U3.5 (D2), U3.6 (D3), U3.8 (GND), U3.9 (~PE), U4.3 (D0), U4.4 (D1), U4.5 (D2), U4.6 (D3), U4.8 (GND), U4.9 (~PE), U5.3 (D0), U5.4 (D1), U5.5 (D2), U5.6 (D3), U5.8 (GND), U5.9 (~PE), U6.3 (D0), U6.4 (D1), U6.5 (D2), U6.6 (D3), U6.8 (GND), U6.9 (~PE), U7.7 (GND), U8.7 (GND), U9.7 (GND), U10.7 (GND), U11.7 (GND), U12.7 (GND), U13.7 (GND), U14.7 (GND), U15.7 (GND), U16.7 (GND), U17.7 (GND), U18.7 (GND), U19.7 (GND), U20.7 (GND), U21.3 (D0), U21.4 (D1), U21.5 (D2), U21.6 (D3), U21.8 (GND), U21.9 (~PE), U22.8 (GND), U22.10 (I0b), U22.11 (I1b), U22.12 (I2b), U22.13 (I3b), U23.3 (D0), U23.4 (D1), U23.5 (D2), U23.6 (D3), U23.8 (GND), U23.9 (~PE), U24.1 (OEa), U24.8 (GND), U24.10 (I0b), U24.11 (I1b), U24.12 (I2b), U24.13 (I3b), U25.7 (GND), U26.3 (D0), U26.4 (D1), U26.5 (D2), U26.6 (D3), U26.8 (GND), U26.9 (~PE), U27.8 (GND), U27.10 (I0b), U27.11 (I1b), U27.12 (I2b), U27.13 (I3b), U28.3 (D0), U28.4 (D1), U28.5 (D2), U28.6 (D3), U28.8 (GND), U28.9 (~PE), U29.1 (OEa), U29.8 (GND), U29.10 (I0b), U29.11 (I1b), U29.12 (I2b), U29.13 (I3b), U30.1 (OE), U30.10 (GND), U31.8 (GND), U32.3 (A2), U32.4 (E1), U32.5 (E2), U32.8 (GND), U33.8 (GND), U34.8 (GND), U34.9 (S2), U35.8 (GND), U35.9 (S2), U36.8 (GND), U36.9 (S2), U36.10 (S1), U37.8 (GND), U37.9 (S2), U37.10 (S1), U38.8 (GND), U38.9 (S2), U38.10 (S1), U39.8 (GND), U39.9 (S2), U39.10 (S1), U40.1 (Ea), U40.3 (I3a), U40.8 (GND), U40.13 (I3b), U40.15 (Eb), U41.1 (Ea), U41.3 (I3a), U41.8 (GND), U41.13 (I3b), U41.15 (Eb), U42.4 (E1), U42.5 (E2), U42.8 (GND), U43.7 (V_{SS}), U43.12, U44.7 (V_{SS}), U44.12, U45.7 (V_{SS}), U45.12, U46.7 (V_{SS}), U46.12, U47.7 (V_{SS}), U47.12, U48.7 (V_{SS}), U48.12, U49.7 (V_{SS}), U49.12, U50.7 (V_{SS}), U50.12, U51.7 (V_{SS}), U51.12, U52.7 (V_{SS}), U52.12, U53.7 (V_{SS}), U53.12, U54.7 (V_{SS}), U54.12, U55.7 (V_{SS}), U55.12, U56.7 (V_{SS}), U56.12, U57.7 (V_{SS}), U57.12, U58.7 (V_{SS}), U58.12, U59.7 (GND), U60.6 (Inh), U60.7 (VEE), U60.8 (VSS), U61.7 (GND), U62.4 (E1), U62.8 (GND), U63.4 (E1), U63.5 (E2), U63.8 (GND), U64.7 (GND), U65.7 (GND), U66.7 (GND), U68.5 (EI), U68.8 (GND), U69.7 (GND), U70.10 (GND), U71.14 (GND), U71.20 (~CS), U72.10 (GND), U73.10 (GND), U73.17 (I3b), U74.10 (GND), U75.10 (GND), U75.17 (I3b), U76.7 (GND), U77.10 (GND), U78.8 (GND), U79.8 (GND), U80.8 (GND), U81.6 (D3), U81.8 (GND), U82.10 (GND), U83.7 (GND), U90.7 (GND), U91.4 (E1), U91.5 (E2), U91.8 (GND), U100.1 (OE), U100.10 (GND), U101.1 (OE), U101.10 (GND), U101.18 (D7), U102.3 (D0), U102.4 (D1), U102.5 (D2), U102.6 (D3), U102.8 (GND), U102.9 (~PE), U103.7 (GND), U104.7 (GND), U105.3 (A2), U105.4 (E1), U105.5 (E2), U105.8 (GND), U106.7 (GND), U106.12, U106.13, U110.7 (GND), U111.7 (GND), U112.7 (GND), U113.7 (GND), U114.7 (GND), U115.7 (GND), U118.7 (GND), U119.7 (GND), U127.7 (GND), U128.7 (GND), U129.7 (GND), U136.7 (GND), U137.7 (GND)
LoadPixelData: J17.4, J51.1, J85.1, J100.4, U24.7 (Za), U30.11 (LE)
unnamed: U11.3, U11.4
unnamed: U11.10, U11.11
unnamed: U18.2, U18.6
unnamed: U18.10, U18.11
unnamed: U18.13, U20.8
unnamed: U25.1, U90.3
unnamed: U25.2, U90.6
unnamed: U25.4, U90.8
unnamed: U25.5, U90.11
unnamed: U59.1, U64.8
unnamed: U59.2, U59.6
unnamed: U59.10, U59.11
unnamed: U65.8, U66.5
unnamed: U66.2, U66.6
unnamed: U76.1, U83.8
unnamed: U76.2, U83.13
unnamed: U105.14 (O1), U106.1
unnamed: U105.13 (O2), U106.4
unnamed: U105.12 (O3), U106.9
unnamed: U9.3, U110.12
unnamed: U9.6, U110.13
unnamed: U18.9, U112.8
unnamed: U113.8, U114.5
unnamed: U13.8, U114.1
unnamed: U114.2, U114.6
unnamed: U114.3, U114.4, U115.9
unnamed: U18.8, U18.12, U115.1
unnamed: U18.3, U18.4, U115.4
unnamed: U19.8, U119.4
unnamed: U19.3, U119.5
unnamed: U127.2, U129.3
unnamed: U59.9, U127.4
unnamed: U69.8, U127.5
unnamed: U127.8, U129.6
unnamed: U65.6, U127.11
unnamed: U59.5, U129.8
Page13: J59.6, U25.3, U73.8 (I3a)
Page14: J59.7, U25.6, U73.11 (I0b)
PixelClock: J46.4, J51.2, J85.2, J104.4, U29.7 (Za), U31.2 (CP), U33.11 (S0), U34.11 (S0), U35.11 (S0), U36.11 (S0), U37.11 (S0), U38.11 (S0), U39.11 (S0)
~BitmapRead: J59.3, U70.19 (CE), U74.1 (OEa), U74.19 (OEb), U75.1 (OEa), U75.19 (OEb), U83.12, U137.5
~Blank: U68.2 (I5), U69.3, U127.10
~Border: J15.1, J98.1, U68.10 (IO), U127.6
~ExtAdd: J59.2, U72.1 (OEa), U72.19 (OEb), U73.1 (OEa), U73.19 (OEb), U77.1 (OEa), U82.1 (OEa), U83.6, U83.9
~ExtRead: J4.3, J59.4, U82.19 (OEb), U83.5, U137.4
~ExtWrite: J4.2, J59.5, U71.27 (~WE), U77.19 (OEb), U83.4
~External: J14.3, J97.3, R9.1, U68.1 (I4), U69.2
~Format: J7.6, J10.1, J89.1, J93.6, U8.2, U9.4, U19.10
~HBlank: U65.5, U66.3, U66.4
~HCountEnable: J7.3, J14.5, J46.2, J51.3, J85.3, J93.3, J97.5, J104.2, U27.1 (OEa), U68.12 (I2), U69.5, U115.6, U128.1, U136.1
~HFetchEnable: J7.4, J93.4, U115.8
~HLoadEnable: J7.1, J17.2, J93.1, J100.2, U22.1 (OEa), U115.3, U118.1
~HLoad: J62.1, J73.1, U78.2 (CP), U79.2 (CP), U80.2 (CP), U81.2 (CP)
~HSync: J15.2, J62.2, J73.2, J98.2, U59.3, U59.4, U68.3 (I6), U69.12, U102.2 (CP), U104.9
~ReadEnable: U71.22 (~OE), U137.6
~ResetX: J10.3, J14.2, J89.3, J97.2, U1.1 (~MR), U2.1 (~MR), U3.1 (~MR), U8.9, U10.8, U66.1
~ResetY: J10.4, J14.1, J89.4, J97.1, U4.1 (~MR), U5.1 (~MR), U6.1 (~MR), U59.13, U110.11
~Sprite: J14.4, J97.4, R10.1, U68.13 (I3), U69.4
~Tile: J14.6, J97.6, R11.1, U68.11 (I1), U69.6
~VCountEnable: J7.2, J93.2, U115.2, U115.5, U115.10, U119.6
~VSync: J15.3, J62.3, J73.3, J98.3, U59.8, U59.12, U65.4, U68.4 (I7), U69.11, U78.1 (~MR), U79.1 (~MR), U80.1 (~MR), U81.1 (~MR), U104.1
